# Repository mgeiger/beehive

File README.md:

# Overview
Source code for local beehive monitoring.
Project includes all sensor 

# Todo
- [ ] Layout the Hardware system 
- [ ] Figure out if I'm going to use the AD Convertor (ADS1x15)
- [ ] Investigae Weight Sensor system
- [ ] Need to figure out how to handle the API to get random numbers for the test code system

# Hardware
## Sensor Hardware
1. BMP180
1. DHT22
1. DS18B20 (4 or 5x)
1. Light Sensor ()

### DS18B20
A digital temperature sensor.
This is a "1-wire" sensor that can be connected in parallel.
All sensors share the same pin and will only need 4.7K resistor between them all if they are connected in parallel.
You can run in parasite mode. Data and ground just connects, you don't need to connect the power positive.
You can sample every 750ms.
The waterproof item will have three leads: red, black, yellow.
Red goes to the power positive connection.
Black goes to the negative or ground rail.
The yellow will connect to the GPIO pin, with a 4.7-10K from data to 3.3V.

You will need to setup onewire support on the Raspberry Pi.
In /boot/config.txt, add the following to the bottom:
dtoverlay=w1-gpio

run the following after a reboot:
- sudo modprobe w1-gpio
- sudo modprobe w1-therm
- cd /sys/bus/w1/devices
- ls
- cd 28-xxxxx (Change this to match what your serial number is)
- cat w1_slave

The first two lines...I'm not too sure what is going on there. I need to get more information.

If you read the output from w1_slave, you will see t= which is the temperature in 1000ths of degrees celcius.
The "crc=da YES" means the sensor is working, you should check for that.

### BMP180
You can get altitude, temperature and pressure off this system. 

You need to enable i2c on raspi-config.
Reboot the system.
Install the following: python-smbus i2c-tools.
Check to see if i2c is enabled: lsmod | grep i2c_. Look for something like i2c_bcm2708.

For Model A, B rev 2, or B+, run sudo i2cdetect -y 1
For Mobel B rev 1, sudo i2cdetect -y 0

You need to setup the GPIO for this,
VCC - 3.3V P1-01
GND - Ground P1-06
SCL i2c SCL P1-05
SDA i2c SDA P1-03
3.3V Not needed.

For python
import smbus
smbus.SMBus(0) or 1

There is some code here: https://bitbucket.org/MattHawkinsUK/rpispy-misc/raw/master/python/bmp180.py

### DHT22
I like this one more than the DHT11. 

You can only query this every once or two seconds. DHT22 has a resolution of 0.5degC with 2-5% RH.

Pins:
1. VCC 3.3 to 5V (left most when look at front with pins down)
2. Data Out
3. NC
4. Ground Wire

You need to put a 10k pullup between VCC and the data pin.

You need to have to pip items installed RPi (RPi.GPIO as GPIO) and Adafruit_DHT.
I should look at the later and figure out if I can make this cleaner.
There is some good details here:
http://www.home-automation-community.com/temperature-and-humidity-from-am2302-dht22-sensor-displayed-as-chart/

### Analog to Digital Converter (ADC)
I have an ADS1115 at home. It is a 16bit 4-channel ADC. 
VCC to RPi 3.3V
SDA to SDA
SCL to SCL
GND to GND

Use I2C Bus 1 (Pins 3 and 5), not I2C Bus 0 (pins 27 and 28).

This will have the light sensor and the ligth sensor.

## Sensors Locations
- Temperatures
  - Bottom Brood Super
  - Top Brood Super
  - Bottom Honey Super
  - Top Honey Super
  - External
  - Hive Entrance
- Humidity
  - Hive Entrance
  - Middle of Hive
  - External
- Other
  - Altitude
  - Light

# Software
## Database Storage
Will be using Postgres as our database storage. 
The other idea is to use InfluxDB or Graphite. 
Both of these databases are good for time-series data storage.

# Reference
## Blogs to View

Other Setups
------------
- https://hackaday.io/project/2453-arduino-beehive-monitor
- https://hackaday.io/project/1741-honeybee-hive-monitoring
- https://www.kickstarter.com/projects/hivemind/innovative-wireless-beehive-scales/description

##### Video Monitoring
http://dansbeehives.blogspot.com/2013/07/fully-automated-beehive-surveillance.html

##### Bee Monitoring
- http://annemariemaes.net/tag/bee-monitoring/
- http://hivetool.org/w/index.php?title=HiveTool.org

##### Integrating to Xively Feed
https://hackaday.io/project/2453-arduino-beehive-monitor

Datalogging
-----------
- https://www.circuits.dk/datalogger-example-using-sense-hat-influxdb-grafana/
- http://docs.gadgetkeeper.com/pages/viewpage.action?pageId=7700673
- https://rethinkdb.com/blog/temperature-sensors-and-a-side-of-pi/
- http://www.instructables.com/id/Raspberry-Pi-Temperature-Logger/
- https://www.raspberrypi-spy.co.uk/2015/06/basic-temperature-logging-to-the-internet-with-raspberry-pi/
- http://www.instructables.com/id/Raspberry-datalogger-with-Mysql-Highcharts/

With Frontend
-------------
- https://github.com/geerlingguy/temperature-monitor

Database Choice
---------------
- https://mike.depalatis.net/blog/postgres-time-series-database.html
- http://www.postgresqltutorial.com/postgresql-python/connect/
- https://www.raspberrypi.org/forums/viewtopic.php?f=32&t=6335

Battery monitoring
------------------
- https://blog.adafruit.com/2017/01/27/remote-battery-monitoring-piday-raspberrypi-raspberry_pi/

Bee Counting
------------
- http://www.instructables.com/id/Honey-Bee-Counter-II/

Control System
--------------
- https://lifehacker.com/how-to-control-a-raspberry-pi-remotely-from-anywhere-in-1792892937

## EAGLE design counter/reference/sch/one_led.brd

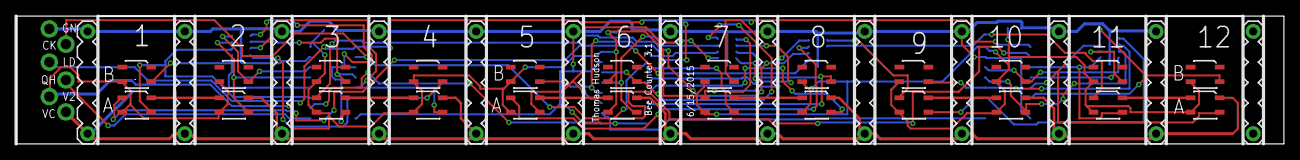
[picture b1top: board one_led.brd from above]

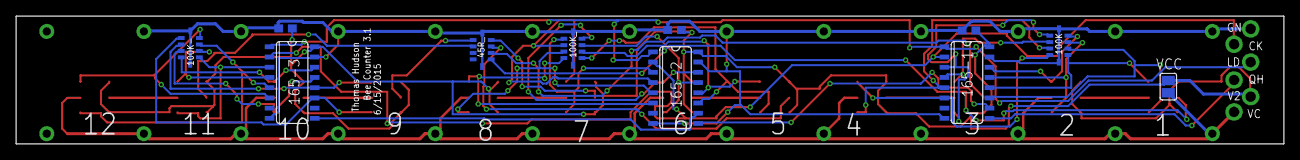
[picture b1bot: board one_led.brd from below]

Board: 2 copper layers, 157.5 x 15.9 mm, 54 parts (11 on the bottom side), 44 nets.

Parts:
1A, 1B, 2A, 2B, 3A, 3B, 4A, 4B, 5A, 5B, 6A, 6B, 7A, 7B, 8A, 8B, 9A, 9B, 10A, 10B, 11A, 11B, 12A, 12B: QRE1113QA; QRE1113
2.1, 2.2, 2.4, 2.5, 2.6, 2.7: M01ADN; 1X01-16GAUGE
45R_, 100K, 100K-, 100K_: RESISTOR-ARRAY_BUSSED; 1608_ARRAY
165-1, 165-2, 165-3: 74165D; SO16
C1-597_1, C15-597_2: 100n; C0603
C-597_3: 100n; C0603
U$1, U$2, U$3, U$4, U$5, U$6, U$7, U$8, U$9, U$10, U$11, U$12, U$13: M06_BEE; 1X06_BEE
VCC: SJ

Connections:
GND: 2.4.1, 45R_.GND1, 45R_.GND2, 100K.GND1, 100K.GND2, 100K-.GND1, 100K-.GND2, 100K_.GND1, 100K_.GND2, 165-1.8, 165-1.15, 165-2.8, 165-2.15, 165-3.8, 165-3.15, C1-597_1.2, C15-597_2.2, C-597_3.2, U$1.1, U$2.1, U$3.1, U$4.1, U$5.1, U$6.1, U$7.1, U$8.1, U$9.1, U$10.1, U$11.1, U$12.1
LOAD: 2.7.1, 165-1.1, 165-2.1, 165-3.1
MISO: 2.5.1, 165-1.9
unnamed: 3A.4, 100K.5, 165-1.3
unnamed: 165-2.10, 165-3.9
unnamed: 1A.4, 100K.2, 165-1.11
unnamed: 3A.2, 45R_.2
unnamed: 165-1.10, 165-2.9
unnamed: 1A.1, 2A.2
unnamed: 1A.2, 45R_.1
unnamed: 3B.4, 100K.6, 165-1.4
unnamed: 5A.1, 6A.2
unnamed: 6A.4, 100K_.3, 165-2.13
unnamed: 5A.2, 45R_.3
unnamed: 1B.4, 100K.1, 165-1.12
unnamed: 2A.4, 100K.3, 165-1.13
unnamed: 2B.4, 100K.4, 165-1.14
unnamed: 3A.1, 4A.2
unnamed: 6B.4, 100K_.4, 165-2.14
unnamed: 7A.1, 8A.2
unnamed: 4A.4, 100K.7, 165-1.5
unnamed: 4B.4, 100K.8, 165-1.6
unnamed: 8A.4, 100K_.7, 165-2.5
unnamed: 8B.4, 100K_.8, 165-2.6
unnamed: 7A.2, 45R_.4
unnamed: 7A.4, 100K_.5, 165-2.3
unnamed: 7B.4, 100K_.6, 165-2.4
unnamed: 5B.4, 100K_.2, 165-2.12
unnamed: 5A.4, 100K_.1, 165-2.11
unnamed: 9A.1, 10A.2
unnamed: 10A.4, 100K-.3, 165-3.13
unnamed: 10B.4, 100K-.4, 165-3.14
unnamed: 11A.1, 12A.2
unnamed: 12A.4, 100K-.7, 165-3.5
unnamed: 12B.4, 100K-.8, 165-3.6
unnamed: 11A.2, 45R_.6
unnamed: 11A.4, 100K-.5, 165-3.3
unnamed: 11B.4, 100K-.6, 165-3.4
unnamed: 9B.4, 100K-.2, 165-3.12
unnamed: 9A.4, 100K-.1, 165-3.11
unnamed: 9A.2, 45R_.5
SCK: 2.6.1, 165-1.2, 165-2.2, 165-3.2
VCC: 2.2.1, 2A.1, 4A.1, 6A.1, 8A.1, 10A.1, 12A.1, U$1.6, U$2.6, U$3.6, U$4.6, U$5.6, U$6.6, U$7.6, U$8.6, U$9.6, U$10.6, U$11.6, U$12.6, VCC.1
VCC1: 1A.3, 1B.3, 2.1.1, 2A.3, 2B.3, 3A.3, 3B.3, 4A.3, 4B.3, 5A.3, 5B.3, 6A.3, 6B.3, 7A.3, 7B.3, 8A.3, 8B.3, 9A.3, 9B.3, 10A.3, 10B.3, 11A.3, 11B.3, 12A.3, 12B.3, 165-1.16, 165-2.16, 165-3.16, C1-597_1.1, C15-597_2.1, C-597_3.1, VCC.2

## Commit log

2016-11-21 Initial commit.
2016-11-22 Generated a requirements.txt file using pipreqs.
2016-12-01 Updates to ignore and database.
2016-12-01 Remove nohup.out.
2016-12-03 Combine all items into one.
2016-12-03 Moved python directory.
2016-12-03 Added in beehive python code.
2016-12-03 Added the start of some sensor tests.
2016-12-09 Updated tests on ADC and DHT
2016-12-10 Added a configuration file.
2017-10-02 Added a beehive counter reference doc.
2017-11-01 Moved requirements file.
2017-12-21 Minor changes to update. Nothing big.
2018-04-18 Minor changes. Move around files.
2018-04-18 Api data store (#7)
    * Minor changes to update. Nothing big.
    * Minor changes. Move around files.
2023-04-17 Bump requests from 2.4.3 to 2.20.0
    Bumps [requests](https://github.com/psf/requests) from 2.4.3 to 2.20.0.
    - [Release notes](https://github.com/psf/requests/releases)
    - [Changelog](https://github.com/psf/requests/blob/main/HISTORY.md)
    - [Commits](https://github.com/psf/requests/compare/v2.4.3...v2.20.0)
    ---
    updated-dependencies:
2023-04-17 Bump flask from 0.11.1 to 1.0
    Bumps [flask](https://github.com/pallets/flask) from 0.11.1 to 1.0.
    - [Release notes](https://github.com/pallets/flask/releases)
    - [Changelog](https://github.com/pallets/flask/blob/main/CHANGES.rst)
    - [Commits](https://github.com/pallets/flask/compare/0.11.1...1.0)
    ---
    updated-dependencies:
2023-05-01 Bump flask from 0.11.1 to 2.3.2
    Bumps [flask](https://github.com/pallets/flask) from 0.11.1 to 2.3.2.
    - [Release notes](https://github.com/pallets/flask/releases)
    - [Changelog](https://github.com/pallets/flask/blob/main/CHANGES.rst)
    - [Commits](https://github.com/pallets/flask/compare/0.11.1...2.3.2)
    ---
    updated-dependencies:
2023-05-23 Bump requests from 2.4.3 to 2.31.0
    Bumps [requests](https://github.com/psf/requests) from 2.4.3 to 2.31.0.
    - [Release notes](https://github.com/psf/requests/releases)
    - [Changelog](https://github.com/psf/requests/blob/main/HISTORY.md)
    - [Commits](https://github.com/psf/requests/compare/v2.4.3...v2.31.0)
    ---
    updated-dependencies:
2024-01-24 Bump requests from 2.4.3 to 2.31.0 (#11)
    Bumps [requests](https://github.com/psf/requests) from 2.4.3 to 2.31.0.
    - [Release notes](https://github.com/psf/requests/releases)
    - [Changelog](https://github.com/psf/requests/blob/main/HISTORY.md)
    - [Commits](https://github.com/psf/requests/compare/v2.4.3...v2.31.0)
    ---
    updated-dependencies:
2024-01-24 Bump flask from 0.11.1 to 2.2.5
    Bumps [flask](https://github.com/pallets/flask) from 0.11.1 to 2.2.5.
    - [Release notes](https://github.com/pallets/flask/releases)
    - [Changelog](https://github.com/pallets/flask/blob/main/CHANGES.rst)
    - [Commits](https://github.com/pallets/flask/compare/0.11.1...2.2.5)
    ---
    updated-dependencies:
2024-01-24 Bump flask from 0.11.1 to 2.2.5 (#12)
    Bumps [flask](https://github.com/pallets/flask) from 0.11.1 to 2.2.5.
    - [Release notes](https://github.com/pallets/flask/releases)
    - [Changelog](https://github.com/pallets/flask/blob/main/CHANGES.rst)
    - [Commits](https://github.com/pallets/flask/compare/0.11.1...2.2.5)
    ---
    updated-dependencies:

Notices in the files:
parts and their libraries:
SparkFun-DigitalIC: Licensing: Creative Commons ShareAlike 4.0 International - https://creativecommons.org/licenses/by-sa/4.0
